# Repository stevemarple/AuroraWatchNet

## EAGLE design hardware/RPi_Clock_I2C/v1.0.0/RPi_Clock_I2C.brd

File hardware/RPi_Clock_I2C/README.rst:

Clock and I2C magnetometer interface for Raspberry Pi
======================================================

This small PCB adds a suitable logic-level interface to the Raspberry
Pi so that it can communicate directly with the AuroraWatchNet
magnetometer sensor head. This method provides a low-cost and easy to
deploy alternative to placing the sensor and microcontroller unit
outside, at the cost of greater temperature dependence and more human
disturbances. The PCB also contains a real-time clock which enables
the Raspberry Pi to start with the correct time when the NTP not
available (such as when the network is down).

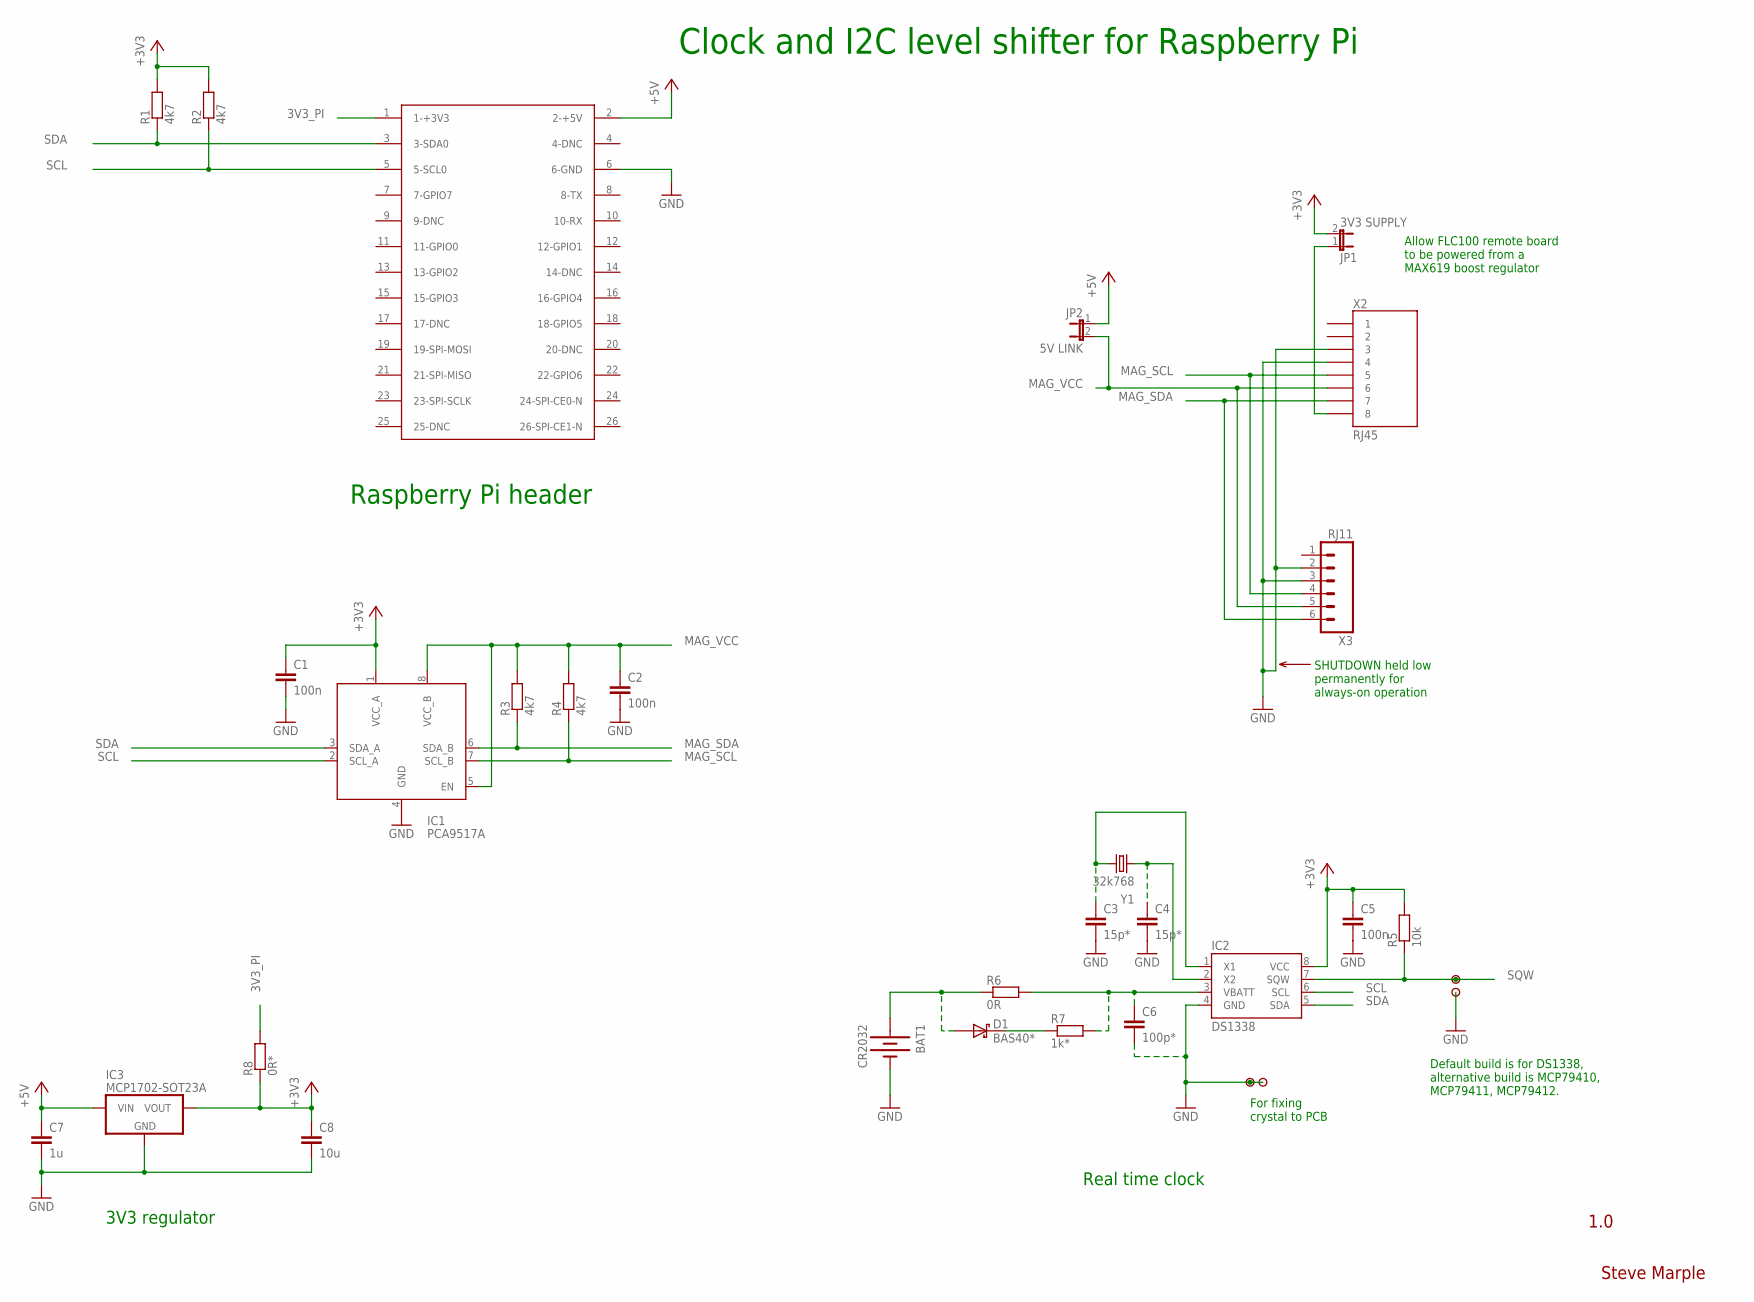
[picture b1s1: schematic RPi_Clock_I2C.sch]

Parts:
BAT1: CR2032; BATTCOM_20MM_PTH
C1, C2, C5: 100n; 1206-HAND
C3, C4: 15p*; 0805-HAND
C6: 100p*; 1206-HAND
C7: 1u; 1206-HAND
C8: 10u; 1206-HAND
D1: BAS40*; SOT23-3-HAND
IC1: PCA9517A; SO08
IC2: DS1338; SO08
IC3: MCP1702-SOT23A; SOT23-3-HAND
JP1: 3V3 SUPPLY; 1X02
JP2: 5V LINK; 1X02
R1, R2, R3, R4: 4k7; 1206-HAND
R5: 10k; 1206-HAND
R6: 0R; 1206-HAND
R7: 1k*; 1206-HAND
R8: 0R*; 1206-HAND
U$1, U$2: PAD
U$3, U$4: PADSMALL; PAD-SMALL
X1: P1; RASPBERRY-PI-HEADER
X2: RJ45; RJ45-8
X3: RJ11; RJ11-6
Y1: 32k768; TC38H

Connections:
3V3_PI: R8.2, X1.1 (1-+3V3)
+3V3: C1.1, C5.1, C8.1, IC1.1 (VCC_A), IC2.8 (VCC), IC3.2 (VOUT), JP1.2, R1.2, R2.2, R5.2, R8.1
+5V: C7.1, IC3.3 (VIN), JP2.1, X1.2 (2-+5V)
GND: BAT1.2 (-), C1.2, C2.2, C3.2, C4.2, C5.2, C6.2, C7.2, C8.2, IC1.4 (GND), IC2.4 (GND), IC3.1 (GND), U$2.1, U$3.1, U$4.1, X1.6 (6-GND), X2.3, X2.4, X3.2, X3.3
MAG_SCL: IC1.7 (SCL_B), R4.1, X2.5, X3.4
MAG_SDA: IC1.6 (SDA_B), R3.1, X2.7, X3.6
MAG_VCC: C2.1, IC1.5 (EN), IC1.8 (VCC_B), JP2.2, R3.2, R4.2, X2.6, X3.5
unnamed: C3.1, IC2.1 (X1), Y1.1
unnamed: D1.3 (C), R7.1
unnamed: C6.1, IC2.3 (VBATT), R6.2, R7.2
unnamed: C4.1, IC2.2 (X2), Y1.2
unnamed: JP1.1, X2.8
SCL: IC1.2 (SCL_A), IC2.6 (SCL), R2.1, X1.5 (5-SCL0)
SDA: IC1.3 (SDA_A), IC2.5 (SDA), R1.1, X1.3 (3-SDA0)
SQW: IC2.7 (SQW), R5.1, U$1.1
VBATT: BAT1.1 (+), D1.1 (A), R6.1

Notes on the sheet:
Real time clock
3V3 regulator
Steve Marple
1.0
SHUTDOWN held low permanently for always-on operation
Raspberry Pi header
Clock and I2C level shifter for Raspberry Pi
Allow FLC100 remote board to be powered from a MAX619 boost regulator
For fixing crystal to PCB
Default build is for DS1338, alternative build is MCP79410, MCP79411, MCP79412.

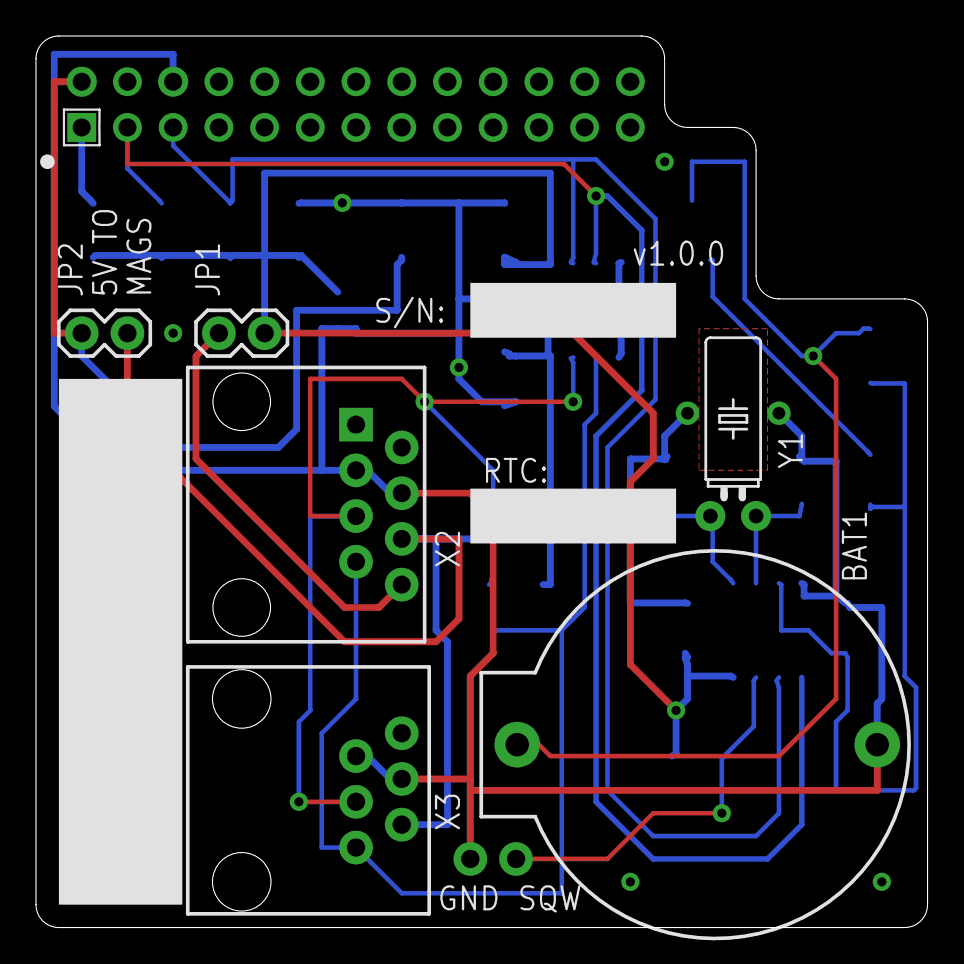
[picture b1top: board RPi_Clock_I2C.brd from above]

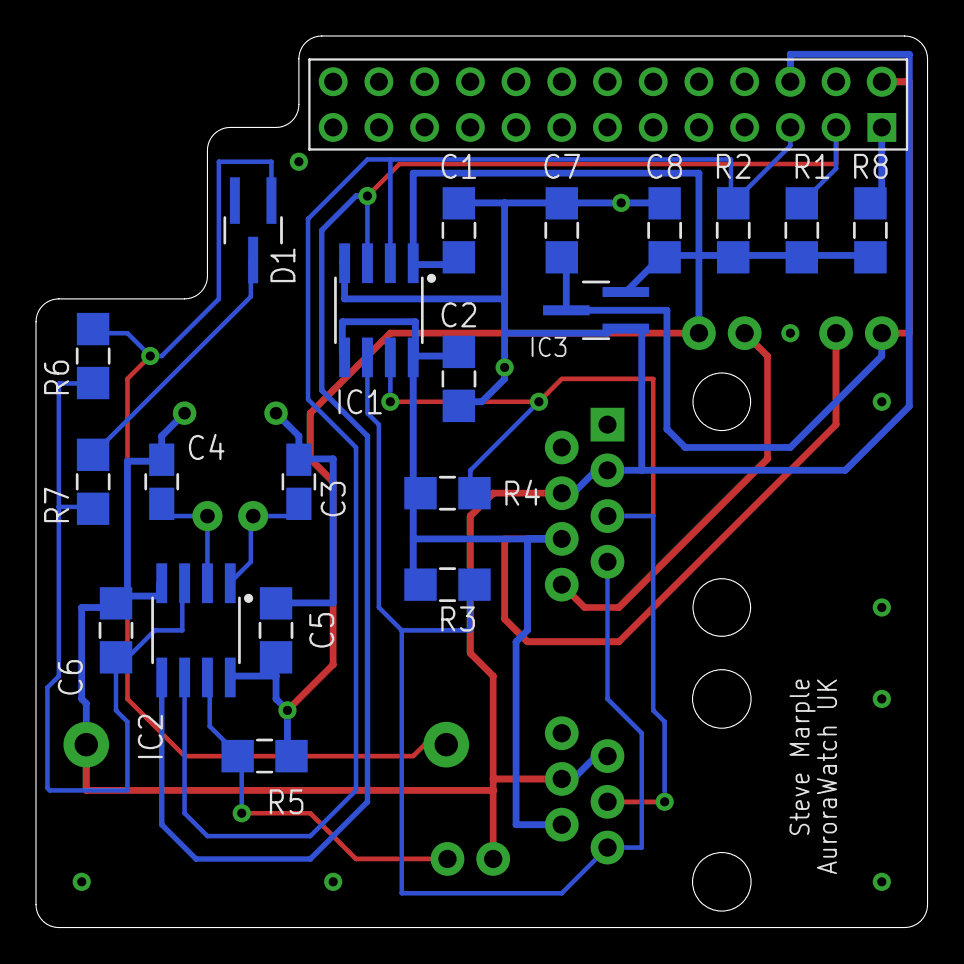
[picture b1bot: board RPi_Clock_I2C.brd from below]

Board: 2 copper layers, 49.5 x 49.5 mm, 31 parts (20 on the bottom side), 16 nets.

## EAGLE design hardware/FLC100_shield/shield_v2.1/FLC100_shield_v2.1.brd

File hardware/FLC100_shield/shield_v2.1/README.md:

FLC100 shield v2.1
==================

Derived from v2.0, with the XRF radio and surface mount PSU removed.

For Power-over-Ethernet use only.

Untested.

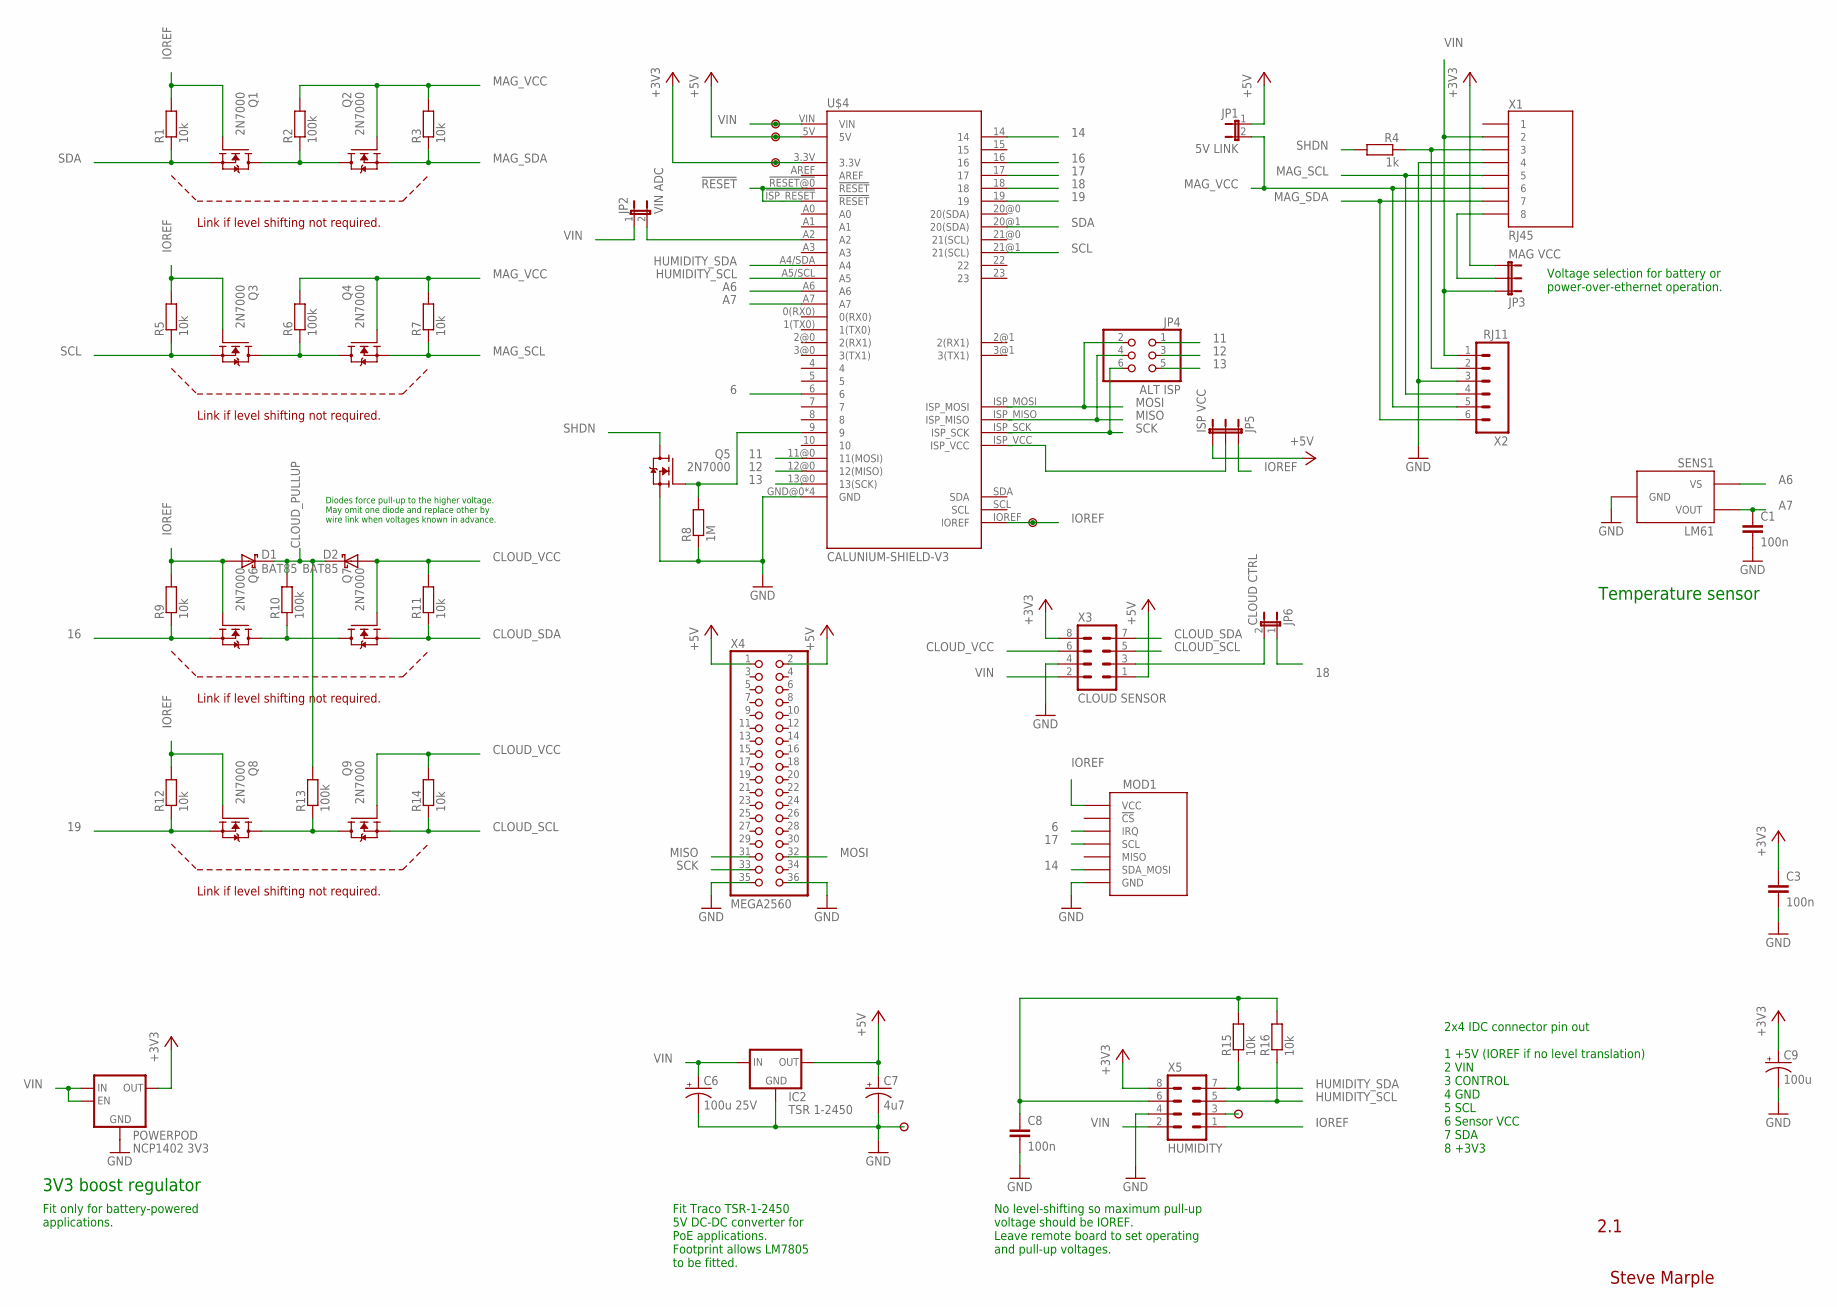
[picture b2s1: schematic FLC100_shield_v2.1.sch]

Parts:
C1, C3, C8: 100n; CAP-PTH-SMALL
C6: 100u 25V; CPOL-RADIAL-100UF-25V-150MIL
C7: 4u7; CPOL-RADIAL-10UF-25V
C9: 100u; CPOL-RADIAL-10UF-25V
D1, D2: BAT85; DIODE-TH-0.4
IC2: TSR 1-2450; 78XXL
JP1: 5V LINK; 1X02
JP2: VIN ADC; 1X02
JP3: MAG VCC; 1X03
JP4: ALT ISP; 2X03
JP5: ISP VCC; 1X03
JP6: CLOUD CTRL; 1X02
MOD1: EMBEDDED_ADVENTURES_MOD-1016NO-HOLES; EMBEDDED_ADVENTURES_MOD-1016-NO-HOLES
POWERPOD: NCP1402 3V3; CISECO_POWERPOD_NCP1402
Q1, Q2, Q3, Q4, Q5, Q6, Q7, Q8, Q9: 2N7000; TO-92
R1, R3, R5, R7, R9, R11, R12, R14, R15, R16: 10k; RES-AXIAL-0.4
R2, R6, R10, R13: 100k; RES-AXIAL-0.4
R4: 1k; RES-AXIAL-0.4
R8: 1M; RES-AXIAL-0.4
SENS1: LM61; TO-92
U$1, U$2, U$3, U$5, U$13, U$14: PAD
U$4: CALUNIUM-SHIELD-V3; CALUNIUM-SHIELD-NO-OUTLINE-NO-HOLES-NO-TEXT-V3
X1: RJ45; RJ45-8
X2: RJ11; RJ11-6
X3: CLOUD SENSOR; ML8
X4: MEGA2560; 2X18
X5: HUMIDITY; ML8

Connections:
6: MOD1.IRQ, U$4.6
11: JP4.1, U$4.11@0 (11(MOSI))
12: JP4.3, U$4.12@0 (12(MISO))
13: JP4.5, U$4.13@0 (13(SCK))
14: MOD1.SDA_MOSI, U$4.14
16: Q6.1 (S), R9.P$1 (1), U$4.16
17: MOD1.SCL, U$4.17
18: JP6.1, U$4.18
19: Q8.1 (S), R12.P$1 (1), U$4.19
!RESET: U$4.!ISP_RESET (!RESET), U$4.!RESET@0 (!RESET)
+3V3: C3.1, C9.1 (+), JP3.3, POWERPOD.VOUT (OUT), U$3.1, U$4.3.3V, X3.8, X5.8
+5V: C7.1 (+), IC2.OUT, JP1.1, JP5.3, U$2.1, U$4.5V, X3.1, X4.1, X4.2
A6: SENS1.1 (VS), U$4.A6
A7: C1.1, SENS1.2 (VOUT), U$4.A7
CLOUD_PULLUP: D1.C, D2.C, R10.P$2 (2), R13.P$2 (2)
CLOUD_SCL: Q9.1 (S), R14.P$1 (1), X3.5
CLOUD_SDA: Q7.1 (S), R11.P$1 (1), X3.7
CLOUD_VCC: D2.A, Q7.2 (G), Q9.2 (G), R11.P$2 (2), R14.P$2 (2), X3.6
GND: C1.2, C3.2, C6.2 (-), C7.2 (-), C8.2, C9.2 (-), IC2.GND, MOD1.GND, POWERPOD.GND, Q5.1 (S), R8.P$1 (1), SENS1.3 (GND), U$4.GND@0 (GND), U$4.GND@1 (GND), U$4.GND@2 (GND), U$4.GND@3 (GND), U$14.1, X1.4, X2.3, X3.4, X4.35, X4.36, X5.4
HUMIDITY_SCL: R16.P$1 (1), U$4.A5/SCL (A5), X5.5
HUMIDITY_SDA: R15.P$1 (1), U$4.A4/SDA (A4), X5.7
IOREF: D1.A, JP5.1, MOD1.VCC, Q1.2 (G), Q3.2 (G), Q6.2 (G), Q8.2 (G), R1.P$2 (2), R5.P$2 (2), R9.P$2 (2), R12.P$2 (2), U$4.IOREF, U$5.1, X5.1
ISP_VCC: JP5.2, U$4.ISP_VCC
MAG_SCL: Q4.1 (S), R7.P$1 (1), X1.5, X2.4
MAG_SDA: Q2.1 (S), R3.P$1 (1), X1.7, X2.6
MAG_VCC: JP1.2, Q2.2 (G), Q4.2 (G), R2.P$2 (2), R3.P$2 (2), R6.P$2 (2), R7.P$2 (2), X1.6, X2.5
MISO: JP4.4, U$4.ISP_MISO, X4.31
MOSI: JP4.2, U$4.ISP_MOSI, X4.32
unnamed: Q1.3 (D), Q2.3 (D), R2.P$1 (1)
unnamed: Q3.3 (D), Q4.3 (D), R6.P$1 (1)
unnamed: JP6.2, X3.3
unnamed: Q6.3 (D), Q7.3 (D), R10.P$1 (1)
unnamed: Q8.3 (D), Q9.3 (D), R13.P$1 (1)
unnamed: R4.P$1 (1), X1.3, X2.2
unnamed: JP3.2, X1.8
unnamed: JP2.2, U$4.A2
unnamed: U$13.1, X5.3
unnamed: C8.1, R15.P$2 (2), R16.P$2 (2), X5.6
unnamed: Q5.2 (G), R8.P$2 (2), U$4.9
SCK: JP4.6, U$4.ISP_SCK, X4.33
SCL: Q3.1 (S), R5.P$1 (1), U$4.21@1 (21(SCL))
SDA: Q1.1 (S), R1.P$1 (1), U$4.20@1 (20(SDA))
SHDN: Q5.3 (D), R4.P$2 (2)
VIN: C6.1 (+), IC2.IN, JP2.1, JP3.1, POWERPOD.ENABLE, POWERPOD.VIN (IN), U$1.1, U$4.VIN, X1.2, X2.1, X3.2, X5.2

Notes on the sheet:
2.1
Steve Marple
Temperature sensor
3V3 boost regulator
Fit only for battery-powered applications.
Fit Traco TSR-1-2450 5V DC-DC converter for PoE applications. Footprint allows LM7805 to be fitted.
Link if level shifting not required.
Voltage selection for battery or power-over-ethernet operation.
No level-shifting so maximum pull-up voltage should be IOREF. Leave remote board to set operating and pull-up voltages.
Diodes force pull-up to the higher voltage. May omit one diode and replace other by wire link when voltages known in advance.
2x4 IDC connector pin out 1 +5V (IOREF if no level translation) 2 VIN 3 CONTROL 4 GND 5 SCL 6 Sensor VCC 7 SDA 8 +3V3

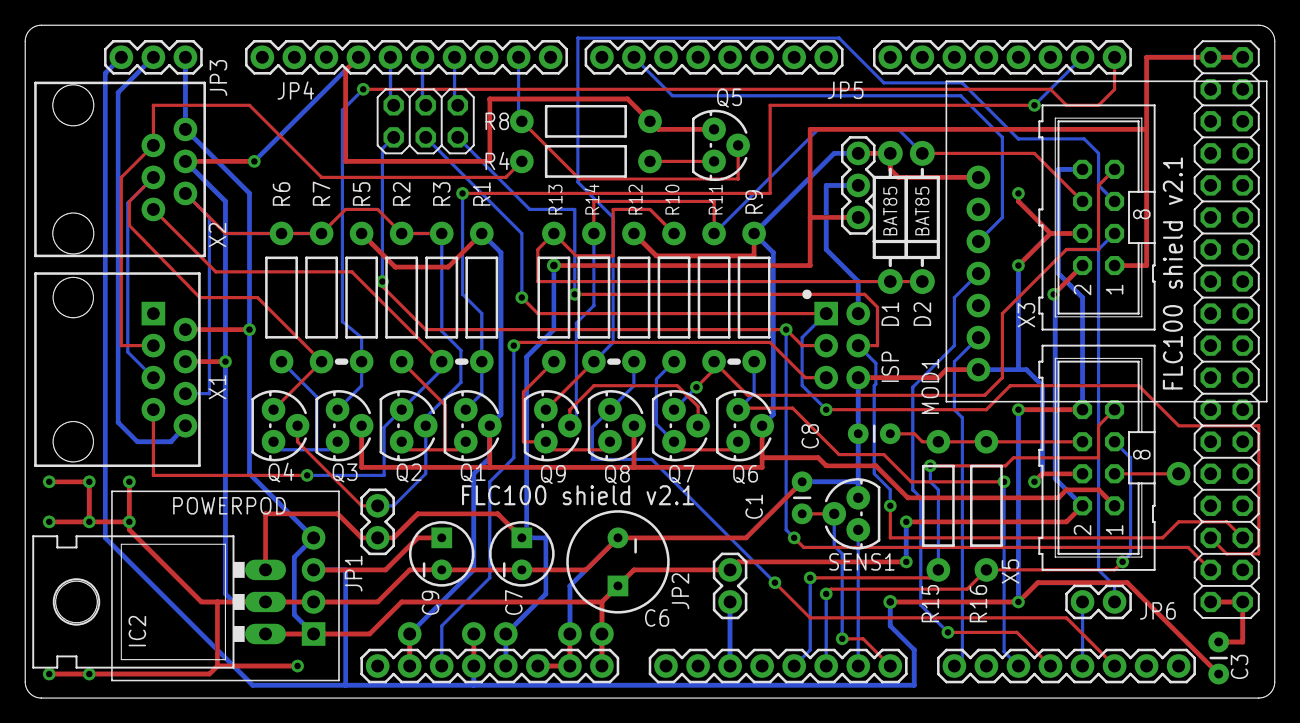
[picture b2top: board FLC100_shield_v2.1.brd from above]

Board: 2 copper layers, 99.1 x 53.3 mm, 55 parts (0 on the bottom side), 44 nets.

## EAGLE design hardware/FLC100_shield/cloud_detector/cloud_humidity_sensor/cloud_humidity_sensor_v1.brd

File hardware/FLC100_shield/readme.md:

# FLC100_shield

Arduino shield for FLC100 magnetometer. A class supporting operation
of the board is provided in the software section of this repository.

## Description

The FLC100_shield supports the operation of the FLC100 magnetometer
for [AuroraWatchNet](http://aurorawatch.net/). The shield can be built
to operate in one of several modes.

* Using the remote FLC100 PCB, digital signals are sent to/from
  the board over I2C. The remote board generates the 5V supply whilst
  the FLC100 shield generates the 3.3V supply. The MCP3424 ADC resides
  on the remote board. This mode allows the sensor and critical
  analogue electronics to be located in a temperature-stabilised
  location (eg buried). Two or three axis operation is possible by
  configuring the MCP3424 ADCs to use different I2C addresses. This is
  the intended mode of operation.
* Fully self-contained, with the FLC100 and MCP3424 ADC located
  on-board. The shield provides both 3.3V and 5V supplies from an
  external 3V battery. This mode is the most compact but may expose
  the sensor to higher temperature variations and stray magnetic
  interference.
* Using the remote FLC100 PCB, analogue signals are sent to the
  MCP3424 ADC on the shield. This mode is likely to result in
  sub-optimal performance and was provided in case of difficulties
  driving I2C signals over the required distance; the concern appears
  unfounded.

## Pin mapping

0: XRF RX (via jumper)  
1: XRF TX (via jumper)  
2: XRF RX (via jumper)  
3: XRF TX (via jumper)  
5: XRF /reset (via jumper)  
7: XRF sleep (via jumper)  
9: MAX619 shutdown  
A2: Vin (via jumper)  
A6: LM61 power  
A7: LM61 output  
SDA/SCL: MCP3424

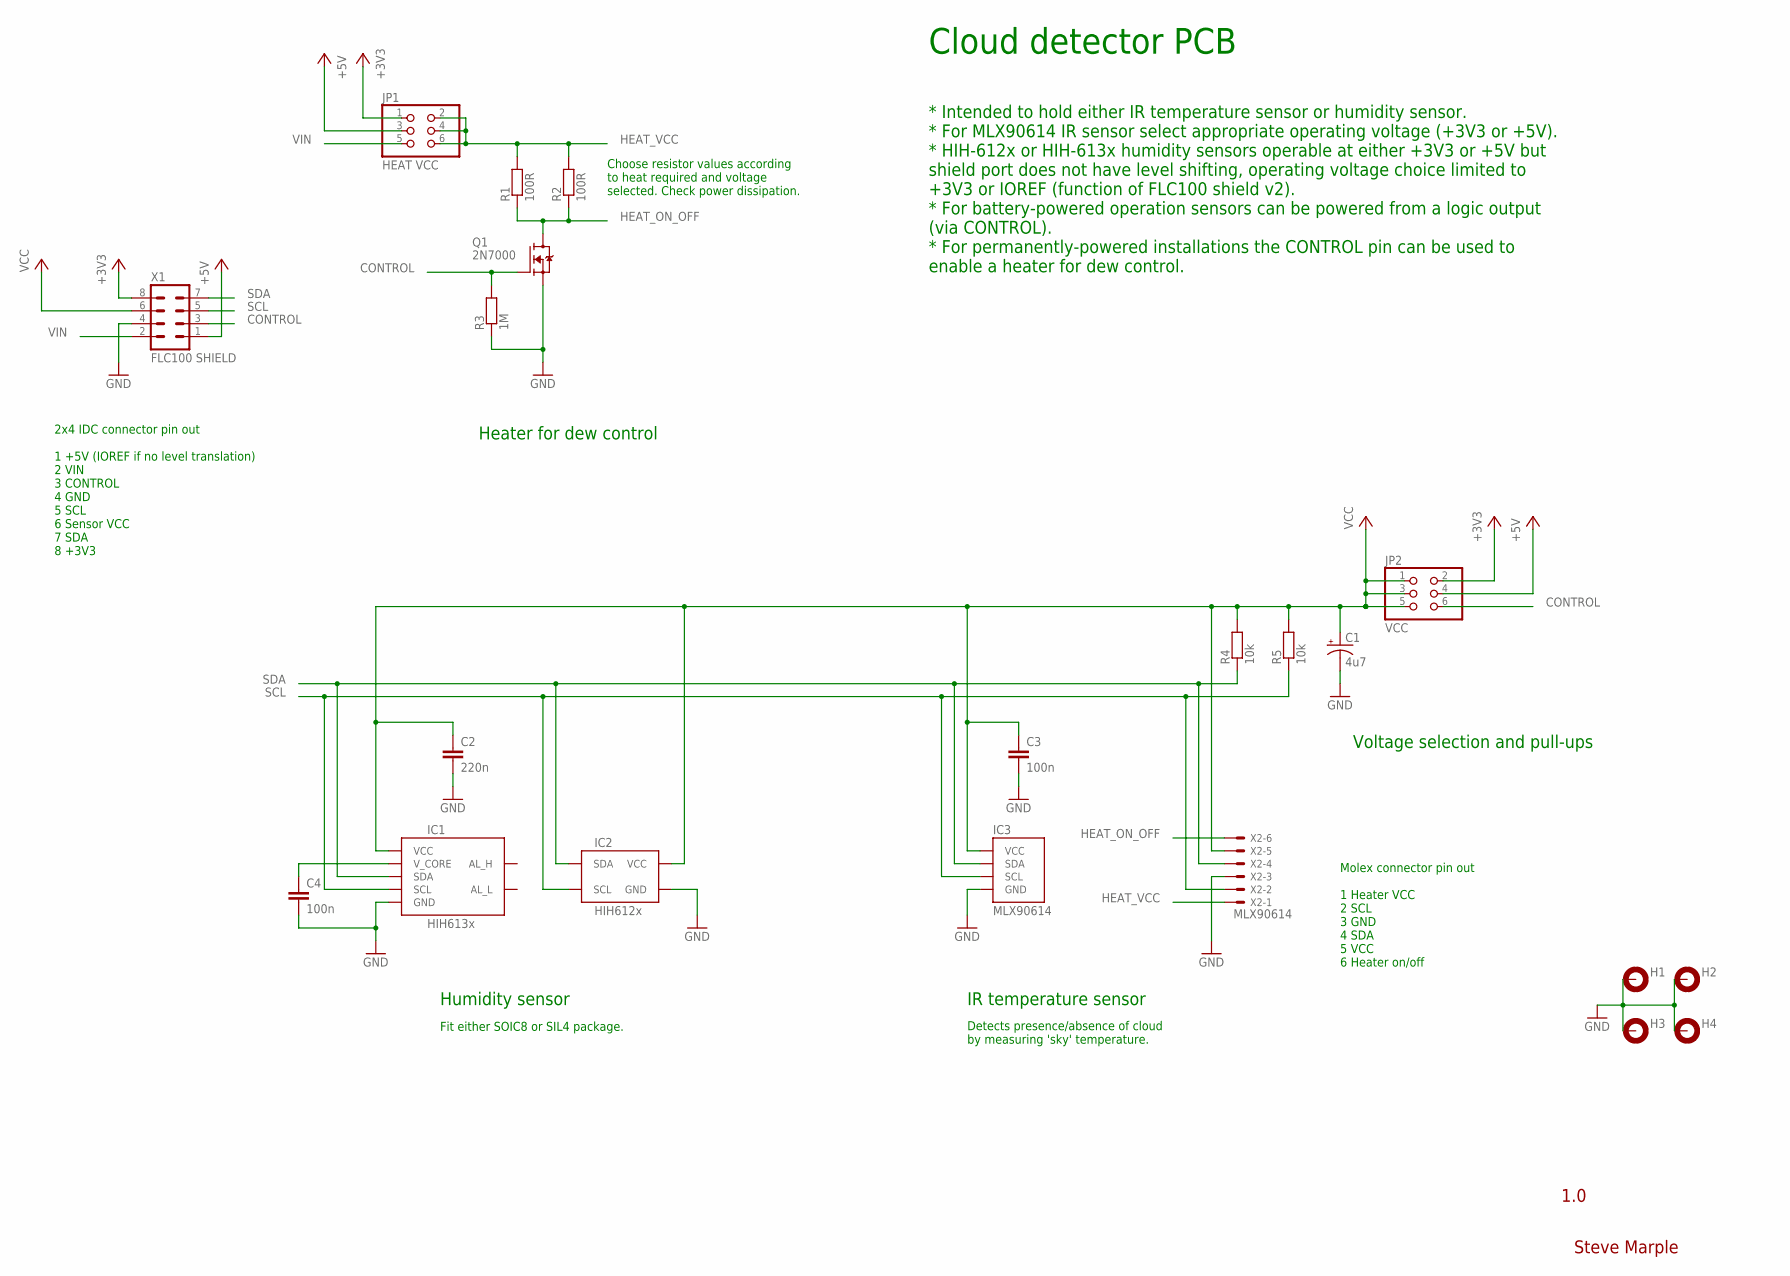
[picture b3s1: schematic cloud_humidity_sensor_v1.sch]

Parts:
C1: 4u7; CPOL-RADIAL-10UF-25V
C2: 220n; CAP-PTH-SMALL
C3, C4: 100n; CAP-PTH-SMALL
H1, H2, H3, H4: MOUNT-PAD-ROUND3.0; 3,0-PAD
IC1: HIH613x; SO08
IC2: HIH612x; SIL04
IC3: MLX90614; TO39-4
JP1: HEAT VCC; 2X03
JP2: VCC; 2X03
Q1: 2N7000; TO-92
R1, R2: 100R; RES-AXIAL-0.4
R3: 1M; RES-AXIAL-0.4
R4, R5: 10k; RES-AXIAL-0.4
X1: FLC100 SHIELD; ML8
X2: MLX90614; 22-23-2061

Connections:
+3V3: JP1.1, JP2.2, X1.8
+5V: JP1.3, JP2.4, X1.1
CONTROL: JP2.6, Q1.2 (G), R3.P$2 (2), X1.3
GND: C1.2 (-), C2.2, C3.2, C4.2, H1.B3,0, H2.B3,0, H3.B3,0, H4.B3,0, IC1.2 (GND), IC2.2 (GND), IC3.4 (GND), Q1.1 (S), R3.P$1 (1), X1.4, X2.3
HEAT_ON_OFF: Q1.3 (D), R1.P$1 (1), R2.P$1 (1), X2.6
HEAT_VCC: JP1.2, JP1.4, JP1.6, R1.P$2 (2), R2.P$2 (2), X2.1
SCL: IC1.3 (SCL), IC2.3 (SCL), IC3.1 (SCL), R5.P$1 (1), X1.5, X2.2
SDA: IC1.4 (SDA), IC2.4 (SDA), IC3.2 (SDA), R4.P$1 (1), X1.7, X2.4
VCC: C1.1 (+), C2.1, C3.1, IC1.8 (VCC), IC2.1 (VCC), IC3.3 (VCC), JP2.1, JP2.3, JP2.5, R4.P$2 (2), R5.P$2 (2), X1.6, X2.5
VIN: JP1.5, X1.2
V_CORE: C4.1, IC1.1 (V_CORE)

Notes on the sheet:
Choose resistor values according to heat required and voltage selected. Check power dissipation.
Humidity sensor
Fit either SOIC8 or SIL4 package.
IR temperature sensor
Detects presence/absence of cloud by measuring 'sky' temperature.
Cloud detector PCB
* Intended to hold either IR temperature sensor or humidity sensor. * For MLX90614 IR sensor select appropriate operating voltage (+3V3 or +5V). * HIH-612x or HIH-613x humidity sensors operable at either +3V3 or +5V but shield port does not have level shifting, operating voltage choice limited to +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
Voltage selection and pull-ups
Heater for dew control
Molex connector pin out 1 Heater VCC 2 SCL 3 GND 4 SDA 5 VCC 6 Heater on/off
2x4 IDC connector pin out 1 +5V (IOREF if no level translation) 2 VIN 3 CONTROL 4 GND 5 SCL 6 Sensor VCC 7 SDA 8 +3V3
1.0
Steve Marple

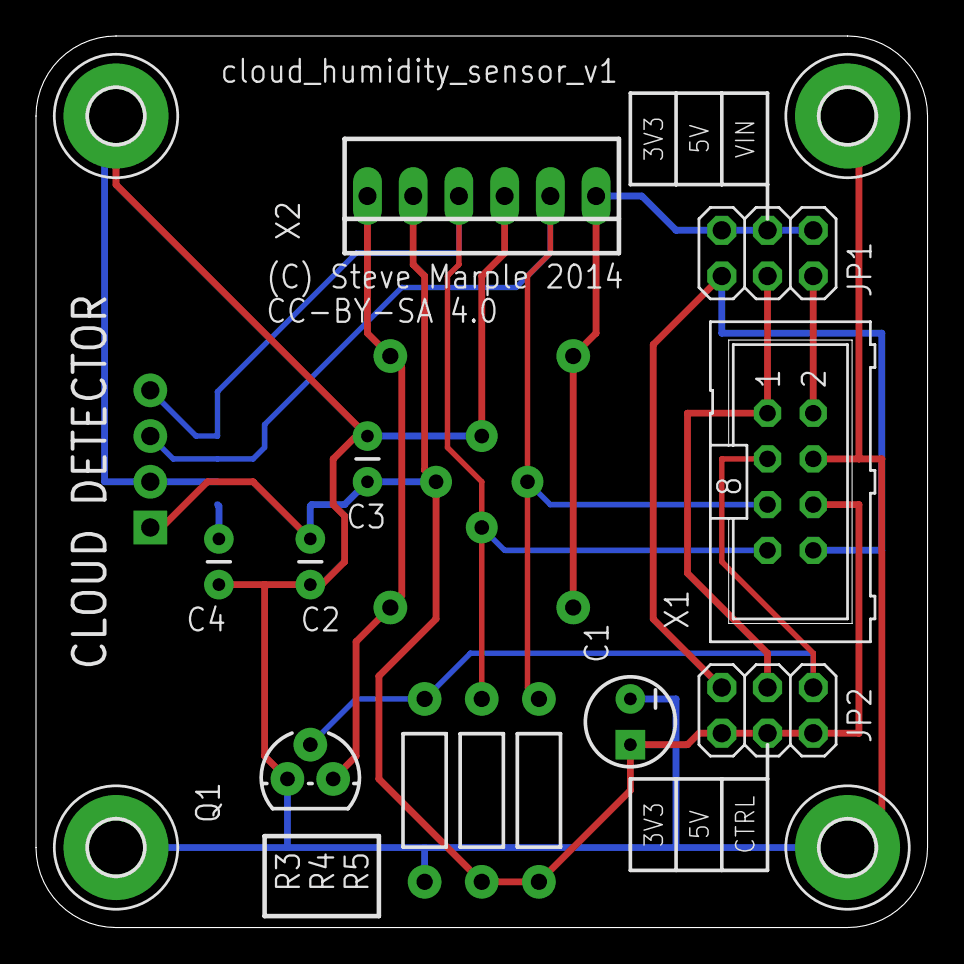
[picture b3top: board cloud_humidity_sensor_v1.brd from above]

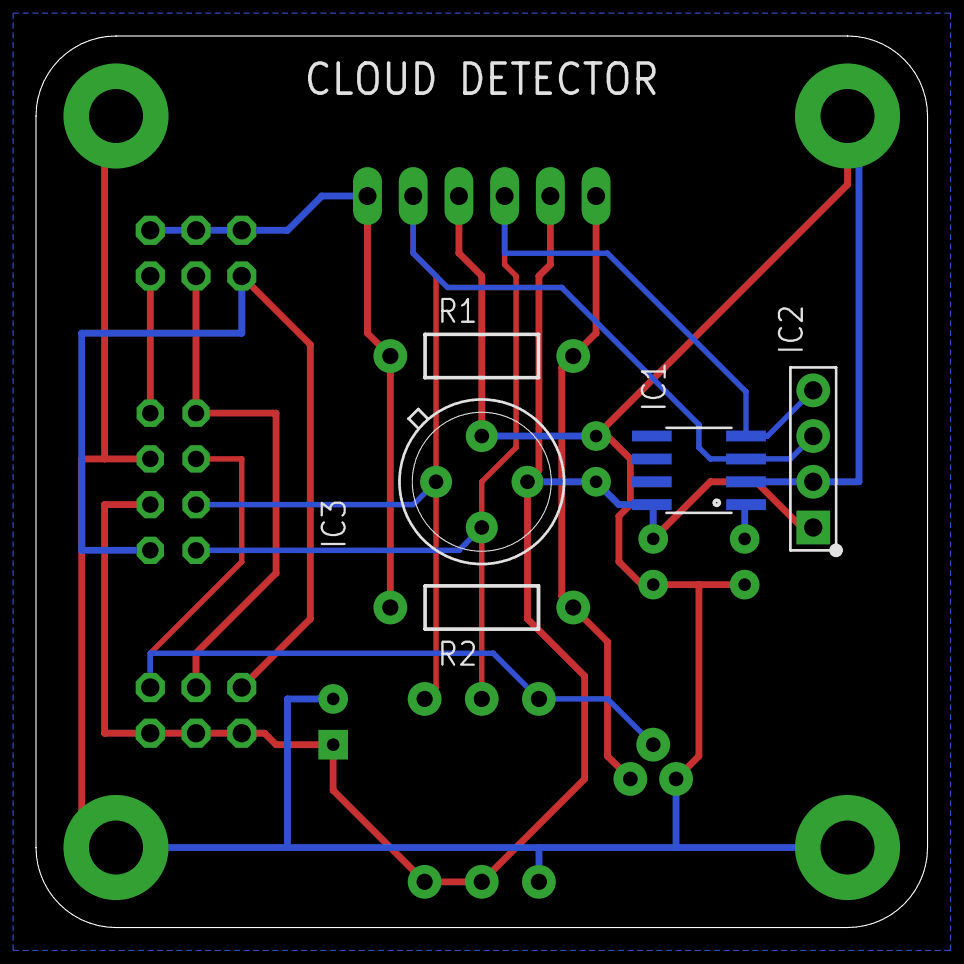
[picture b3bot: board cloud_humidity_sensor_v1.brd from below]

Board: 2 copper layers, 49.5 x 49.5 mm, 21 parts (5 on the bottom side), 11 nets.

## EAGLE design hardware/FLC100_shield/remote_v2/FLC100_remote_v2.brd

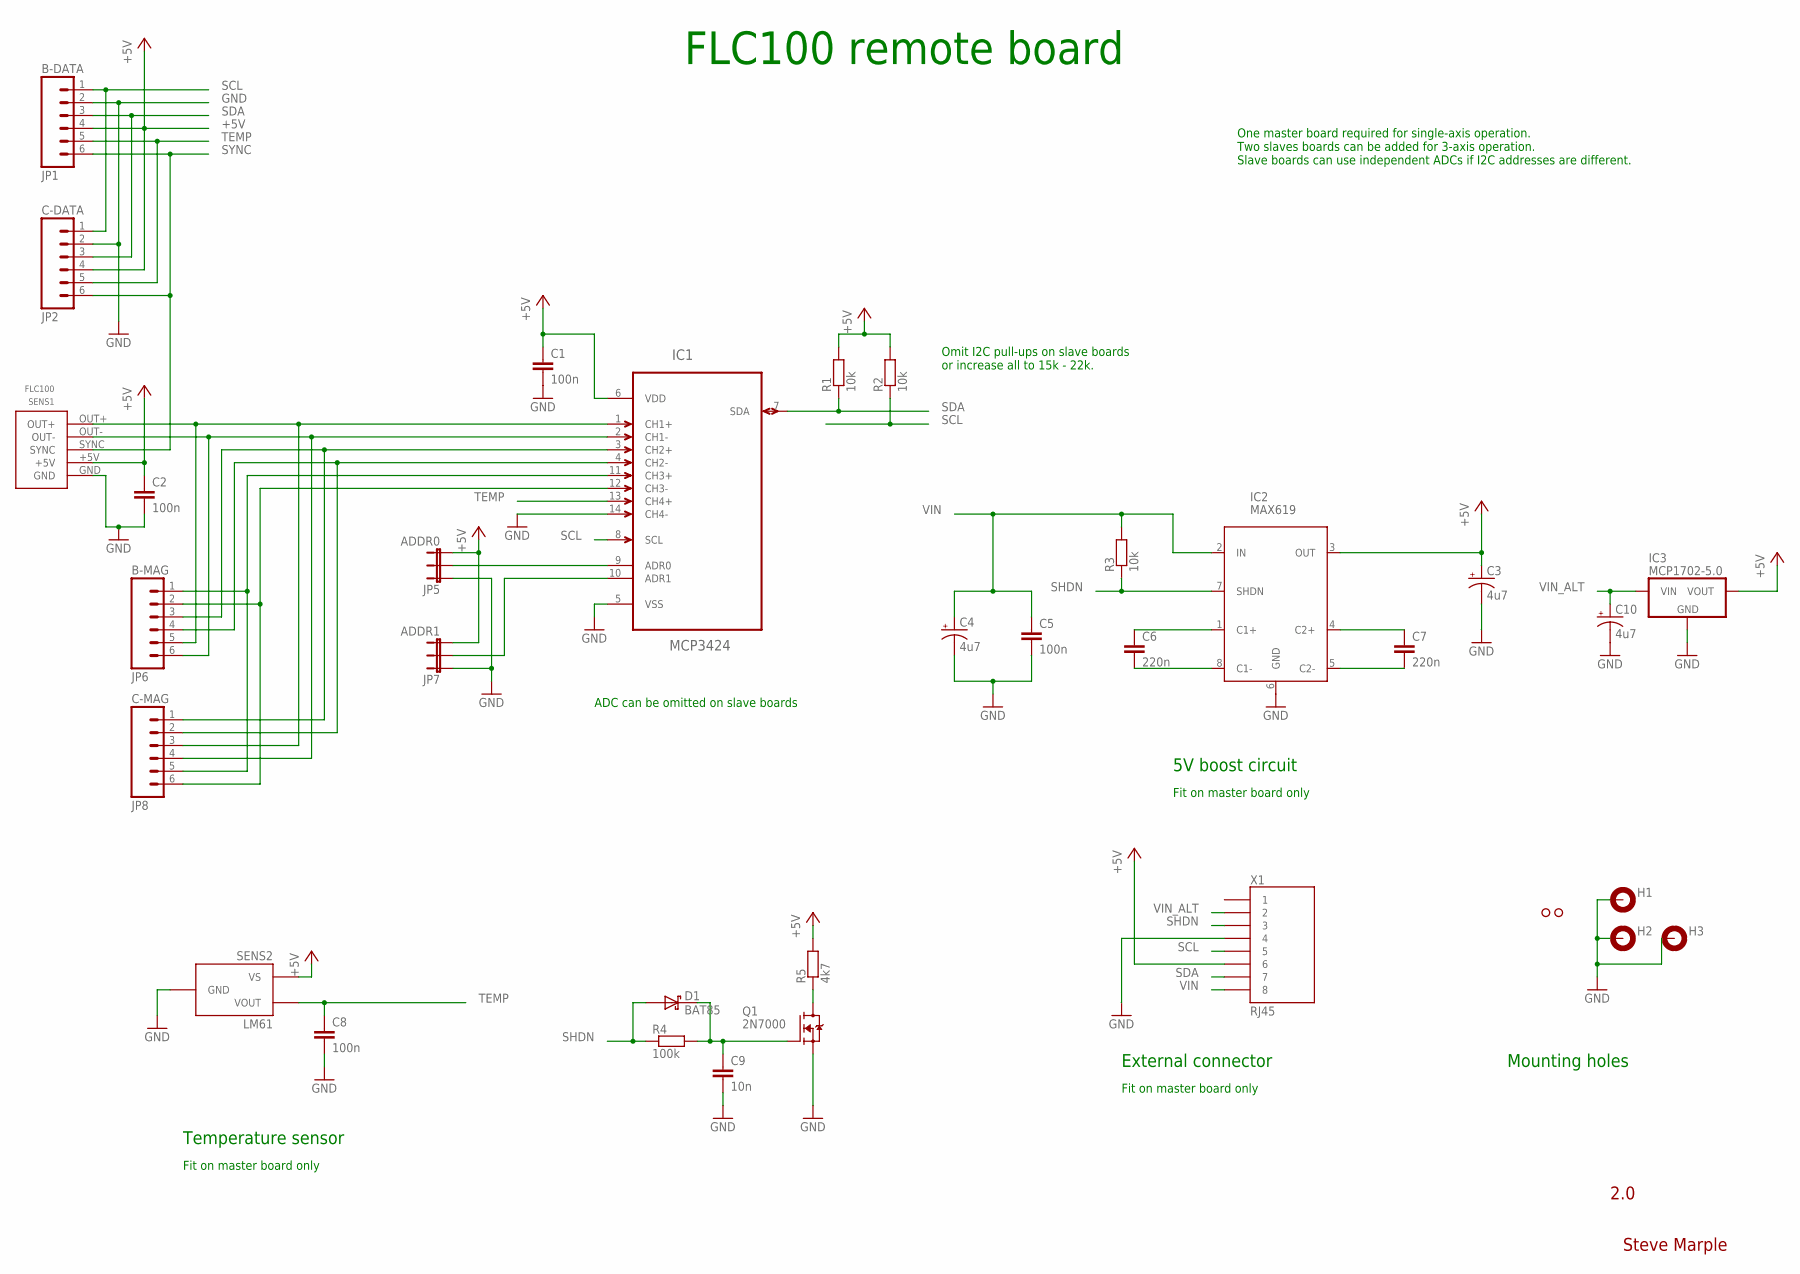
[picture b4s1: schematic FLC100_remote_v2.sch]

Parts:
C1, C2, C5, C8: 100n; CAP-PTH-SMALL
C3, C4, C10: 4u7; CPOL-RADIAL-10UF-25V
C6, C7: 220n; CAP-PTH-SMALL; PART_NO MCRR25221COGJ0100
C9: 10n; CAP-PTH-SMALL
D1: BAT85; DIODE-TH-0.4
H1, H2, H3: MOUNT-PAD-ROUND3.0; 3,0-PAD
IC1: MCP3424; SO14
IC2: MAX619; SO08
IC3: MCP1702-5.0; TO-92
JP1: B-DATA; 1X06_FEMALE
JP2: C-DATA; 1X06_FEMALE
JP5: ADDR0; 1X03
JP6: B-MAG; 1X06_FEMALE
JP7: ADDR1; 1X03
JP8: C-MAG; 1X06_FEMALE
Q1: 2N7000; TO-92
R1, R2, R3: 10k; RES-AXIAL-0.4
R4: 100k; RES-AXIAL-0.4
R5: 4k7; RES-AXIAL-0.4
SENS1: FLC100
SENS2: LM61; TO-92
U$1, U$2: PAD
X1: RJ45; RJ45-8

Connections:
+5V: C1.1, C2.1, C3.1 (+), IC1.6 (VDD), IC2.3 (OUT), IC3.3 (VOUT), JP1.4, JP2.4, JP5.3, JP7.3, R1.P$2 (2), R2.P$2 (2), R5.P$2 (2), SENS1.+5V, SENS2.1 (VS), X1.6
CH1+: IC1.1 (CH1+), JP6.5, JP8.3, SENS1.OUT+
CH1-: IC1.2 (CH1-), JP6.6, JP8.4, SENS1.OUT-
CH2+: IC1.3 (CH2+), JP6.3, JP8.1
CH2-: IC1.4 (CH2-), JP6.4, JP8.2
CH3+: IC1.11 (CH3+), JP6.1, JP8.5
CH3-: IC1.12 (CH3-), JP6.2, JP8.6
GND: C1.2, C2.2, C3.2 (-), C4.2 (-), C5.2, C8.2, C9.2, C10.2 (-), H1.B3,0, H2.B3,0, H3.B3,0, IC1.5 (VSS), IC1.14 (CH4-), IC2.6 (GND), IC3.1 (GND), JP1.2, JP2.2, JP5.1, JP7.1, Q1.1 (S), SENS1.GND, SENS2.3 (GND), X1.4
unnamed: C9.1, D1.C, Q1.2 (G), R4.P$2 (2)
unnamed: Q1.3 (D), R5.P$1 (1)
unnamed: C6.2, IC2.8 (C1-)
unnamed: C6.1, IC2.1 (C1+)
unnamed: IC1.9 (ADR0), JP5.2
unnamed: IC1.10 (ADR1), JP7.2
unnamed: C7.1, IC2.4 (C2+)
unnamed: C7.2, IC2.5 (C2-)
SCL: IC1.8 (SCL), JP1.1, JP2.1, R2.P$1 (1), X1.5
SDA: IC1.7 (SDA), JP1.3, JP2.3, R1.P$1 (1), X1.7
SHDN: D1.A, IC2.7 (SHDN), R3.P$1 (1), R4.P$1 (1), X1.3
SYNC: JP1.6, JP2.6, SENS1.SYNC
TEMP: C8.1, IC1.13 (CH4+), JP1.5, JP2.5, SENS2.2 (VOUT)
VIN: C4.1 (+), C5.1, IC2.2 (IN), R3.P$2 (2), X1.8
VIN_ALT: C10.1 (+), IC3.2 (VIN), X1.2

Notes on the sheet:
2.0
Steve Marple
External connector
5V boost circuit
ADC can be omitted on slave boards
Fit on master board only
FLC100 remote board
One master board required for single-axis operation. Two slaves boards can be added for 3-axis operation. Slave boards can use independent ADCs if I2C addresses are different.
Omit I2C pull-ups on slave boards or increase all to 15k - 22k.
Mounting holes
Temperature sensor

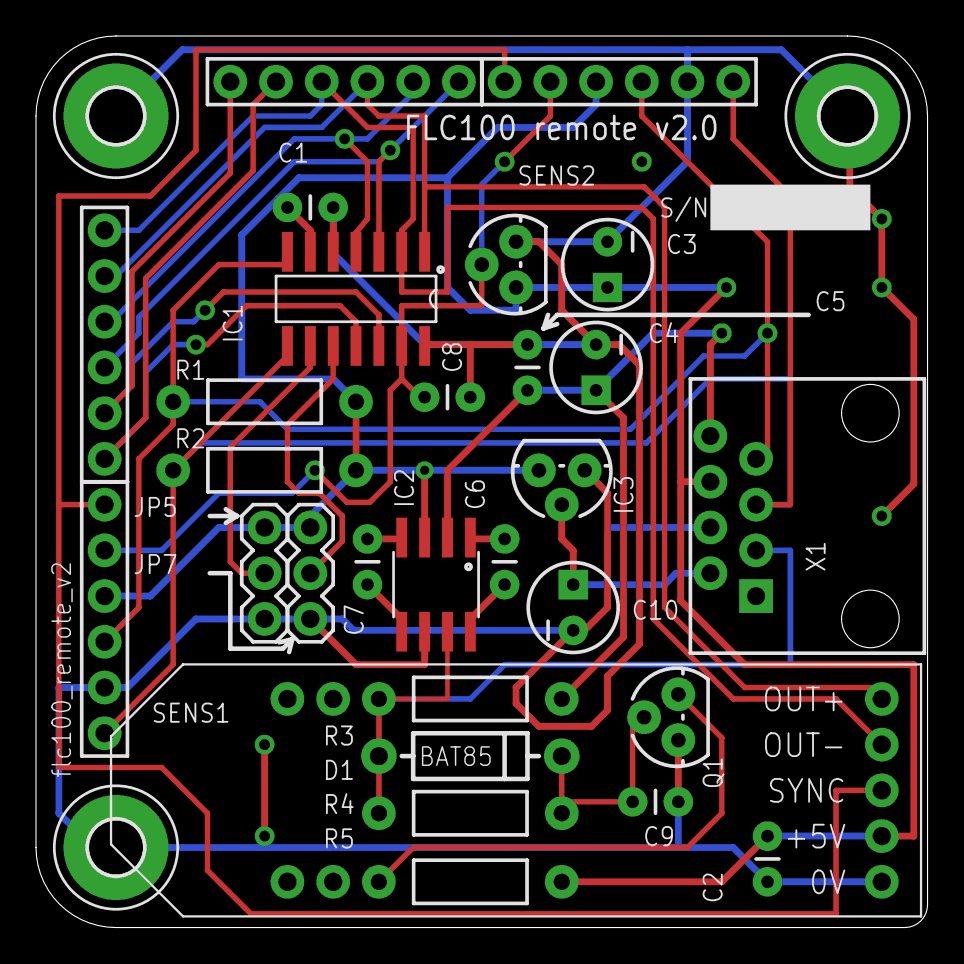
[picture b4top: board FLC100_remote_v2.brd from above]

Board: 2 copper layers, 49.5 x 49.5 mm, 34 parts (0 on the bottom side), 23 nets.

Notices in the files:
hardware/FLC100_shield/cloud_detector/cloud_humidity_sensor/cloud_humidity_sensor_v1.brd:
CC-BY-SA 4.0
parts and their libraries:
SparkFun: Licensing: CC v3.0 Share-Alike You are welcome to use this library for commercial purposes.
